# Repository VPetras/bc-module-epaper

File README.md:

# bc-module-epaper
EPAPER modul for BigClown IoT

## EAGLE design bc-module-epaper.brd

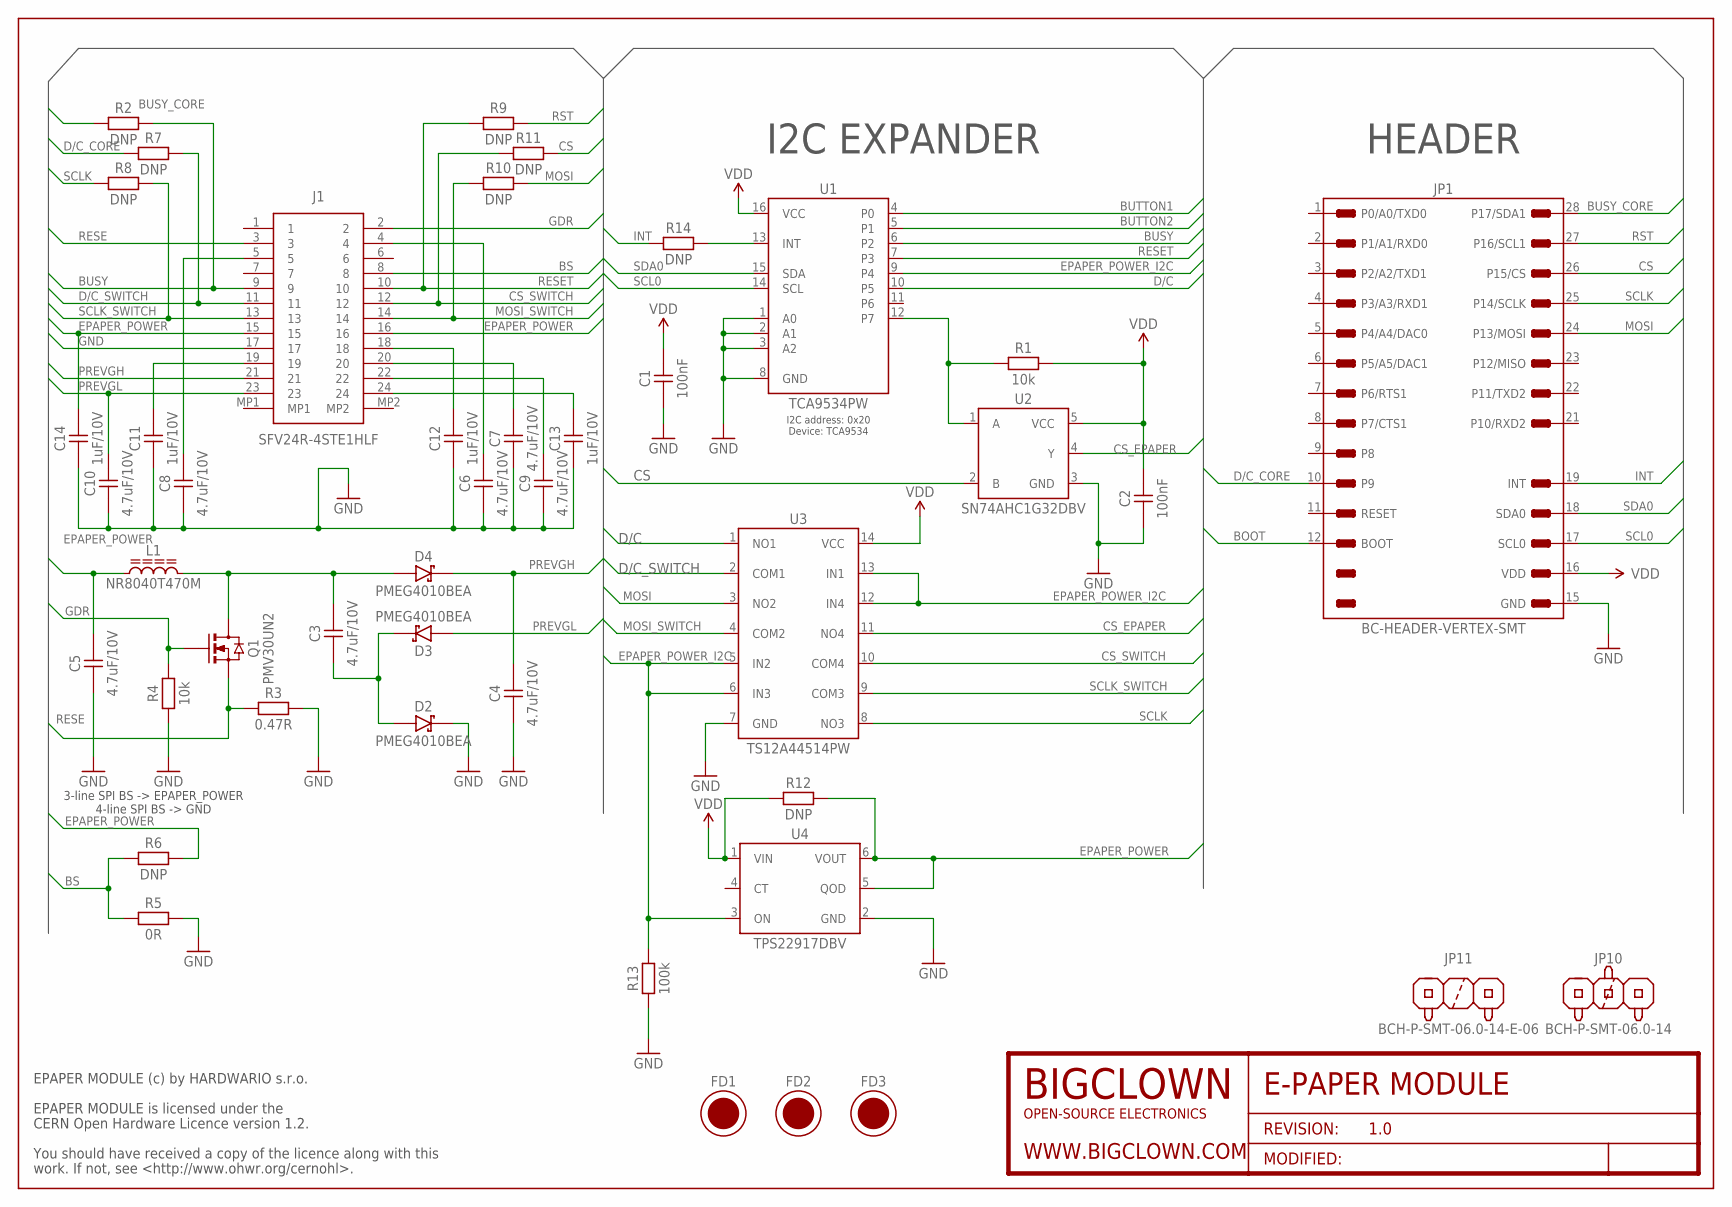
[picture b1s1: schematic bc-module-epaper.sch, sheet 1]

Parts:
C1, C2: 100nF; CAPACITOR-0402_R
C3, C4, C5, C6, C7, C8, C9, C10: 4.7uF/10V; CAPACITOR-0402_R
C11, C12, C13, C14: 1uF/10V; CAPACITOR-0402_R
D2, D3, D4: PMEG4010BEA; SOD-323_R
FD1, FD2, FD3: FIDUCIAL; FIDUCIAL-1MM
FRAME1: FRAME-SCH/A4L-BRD/A4L; FRAME-A4L
J1: SFV24R-4STE1HLF; SFV24R4STE1HLF
JP1: BC-HEADER-VERTEX-SMT; BC-HEADER-MODULE-VERTEX-SMT
JP10: BCH-P-SMT-06.0-14; BCH-P-SMT-14
JP11: BCH-P-SMT-06.0-14-E-06; BCH-P-SMT-14-E-06
L1: NR8040T470M; NR8040T470M_R
Q1: PMV30UN2; SOT-23_R
R1, R4: 10k; RESISTOR-0402_R
R2, R6, R7, R8, R9, R10, R11, R12, R14: DNP; RESISTOR-0402_R
R3: 0.47R; RESISTOR-0402_R
R5: 0R; RESISTOR-0402_R
R13: 100k; RESISTOR-0402_R
U1: TCA9534PW; TCA9534APW_R
U2: SN74AHC1G32DBV; SN74AHC1G32DBV_R
U3: TS12A44514PW; TS12A44514PWR_R
U4: TPS22917DBV; TPS22917DBV_R

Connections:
BOOT: JP1.12 (BOOT)
BS: J1.8, R5.1, R6.1
BUSY: J1.9, R2.2, U1.6 (P2)
BUSY_CORE: JP1.28 (P17/SDA1), R2.1
BUTTON1: U1.4 (P0)
BUTTON2: U1.5 (P1)
CS: JP1.26 (P15/CS), R11.2, U2.2 (B)
CS_EPAPER: U2.4 (Y), U3.11 (NO4)
CS_SWITCH: J1.12, R11.1, U3.10 (COM4)
D/C: U1.10 (P5), U3.1 (NO1)
D/C_CORE: JP1.10 (P9), R7.1
D/C_SWITCH: J1.11, R7.2, U3.2 (COM1)
EPAPER_POWER: C5.1, C14.1, J1.15, J1.16, L1.1, R6.2, R12.2, U4.5 (QOD), U4.6 (VOUT)
EPAPER_POWER_I2C: R13.2, U1.9 (P4), U3.5 (IN2), U3.6 (IN3), U3.12 (IN4), U3.13 (IN1), U4.3 (ON)
GDR: J1.2, Q1.1 (G), R4.2
GND: C1.2, C2.2, C4.2, C5.2, C6.2, C7.2, C8.2, C9.2, C10.2, C11.2, C12.2, C13.2, C14.2, D2.1 (C), J1.17, JP1.15 (GND), R3.2, R4.1, R5.2, R13.1, U1.1 (A0), U1.2 (A1), U1.3 (A2), U1.8 (GND), U2.3 (GND), U3.7 (GND), U4.2 (GND)
INT: JP1.19 (INT), R14.1
MOSI: JP1.24 (P13/MOSI), R10.2, U3.3 (NO2)
MOSI_SWITCH: J1.14, R10.1, U3.4 (COM2)
unnamed: C3.1, D4.2 (A), L1.2, Q1.3 (D)
unnamed: C11.1, J1.19
unnamed: C8.1, J1.5
unnamed: C3.2, D2.2 (A), D3.1 (C)
unnamed: C6.1, J1.4
unnamed: C7.1, J1.20
unnamed: C12.1, J1.18
unnamed: R14.2, U1.13 (INT)
OR_A: R1.2, U1.12 (P7), U2.1 (A)
PREVGH: C4.1, D4.1 (C), J1.21
PREVGL: C10.1, D3.2 (A), J1.23
RESE: J1.3, Q1.2 (S), R3.1
RESET: J1.10, R9.1, U1.7 (P3)
RST: JP1.27 (P16/SCL1), R9.2
SCL0: JP1.17 (SCL0), U1.14 (SCL)
SCLK: JP1.25 (P14/SCLK), R8.1, U3.8 (NO3)
SCLK_SWITCH: J1.13, R8.2, U3.9 (COM3)
SDA0: JP1.18 (SDA0), U1.15 (SDA)
VCOM: C13.1, J1.24
VDD: C1.1, C2.1, JP1.16 (VDD), R1.1, R12.1, U1.16 (VCC), U2.5 (VCC), U3.14 (VCC), U4.1 (VIN)
VSL: C9.1, J1.22

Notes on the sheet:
EPAPER MODULE (c) by HARDWARIO s.r.o.
EPAPER MODULE is licensed under the
CERN Open Hardware Licence version 1.2.
You should have received a copy of the licence along with this
work. If not, see <http://www.ohwr.org/cernohl>.
HEADER
I2C EXPANDER
I2C address: 0x20 Device: TCA9534
3-line SPI BS -> EPAPER_POWER 4-line SPI BS -> GND

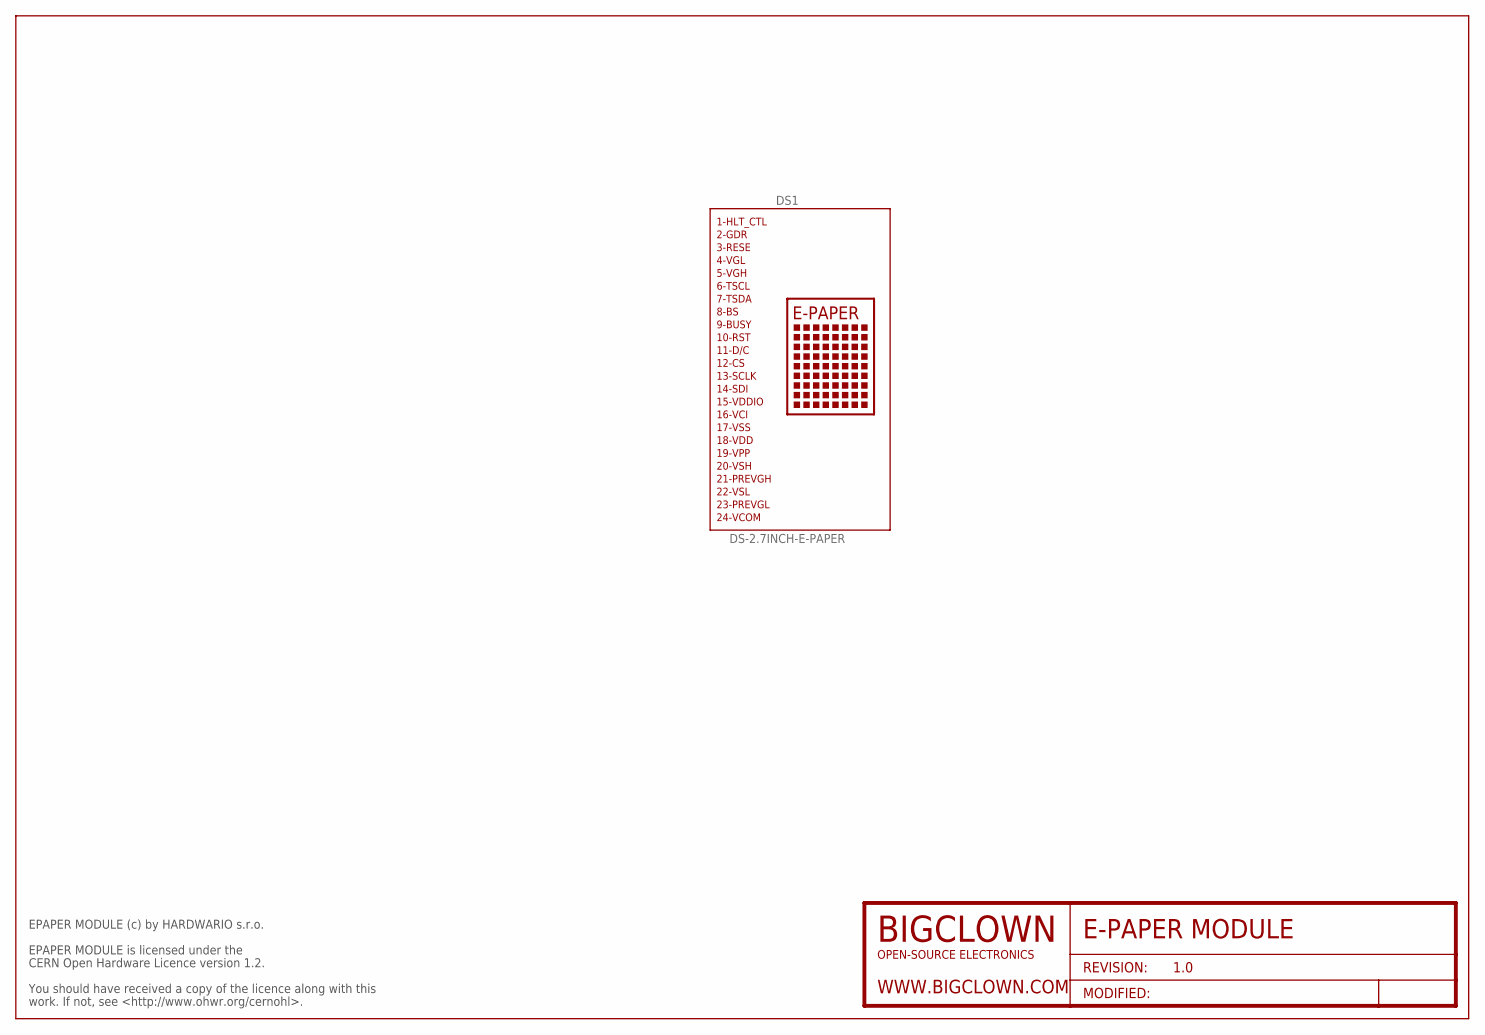
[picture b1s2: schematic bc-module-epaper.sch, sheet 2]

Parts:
DS1: DS-2.7INCH-E-PAPER; 2.7INCH-E-PAPER
FRAME3: FRAME-SCH/A4L-BRD/A4L; FRAME-A4L

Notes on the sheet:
EPAPER MODULE (c) by HARDWARIO s.r.o.
EPAPER MODULE is licensed under the
CERN Open Hardware Licence version 1.2.
You should have received a copy of the licence along with this
work. If not, see <http://www.ohwr.org/cernohl>.

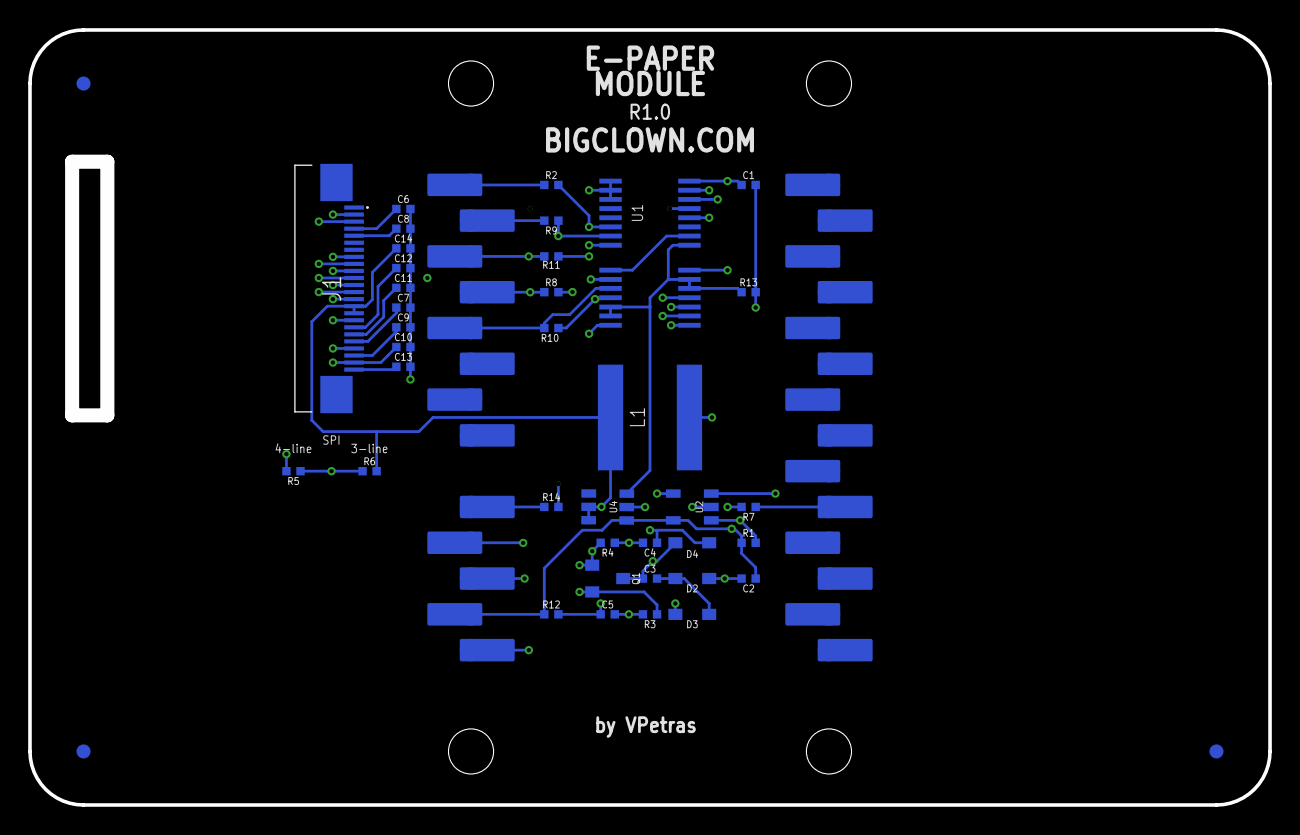
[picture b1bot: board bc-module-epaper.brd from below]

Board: 4 copper layers, 87.3 x 54.3 mm, 47 parts (41 on the bottom side), 37 nets.

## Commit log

2020-02-28 upload files
